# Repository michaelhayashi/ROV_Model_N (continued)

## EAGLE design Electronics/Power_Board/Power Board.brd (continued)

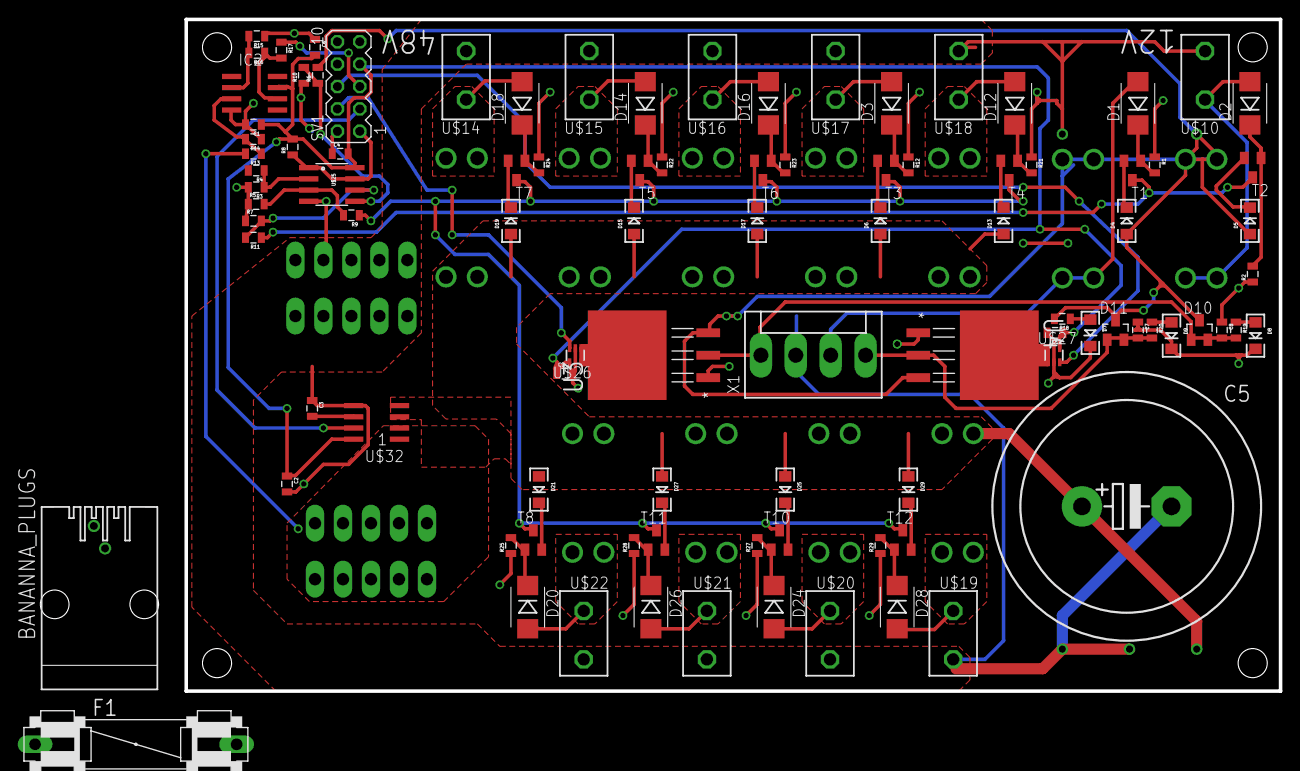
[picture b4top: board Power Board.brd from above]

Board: 2 copper layers, 124.1 x 76.2 mm, 115 parts (1 on the bottom side), 60 nets.

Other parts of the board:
U$23, U$24, U$28, U$29: STAND-OFF

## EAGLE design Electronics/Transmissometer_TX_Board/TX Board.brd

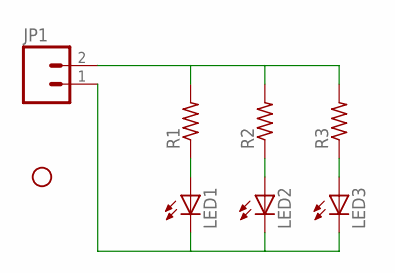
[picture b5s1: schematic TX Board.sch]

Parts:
JP1: M02PTH4; 1X02_XTRA_BIG
JP2: STAND-OFF
LED1, LED2, LED3: LED-FKIT-1206; FKIT-LED-1206
R1, R2, R3: R-US_M1206; M1206

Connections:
GND: JP1.2, R1.2, R2.2, R3.2
unnamed: LED1.A, R1.1
unnamed: LED2.A, R2.1
unnamed: LED3.A, R3.1
unnamed: JP1.1, LED1.C, LED2.C, LED3.C

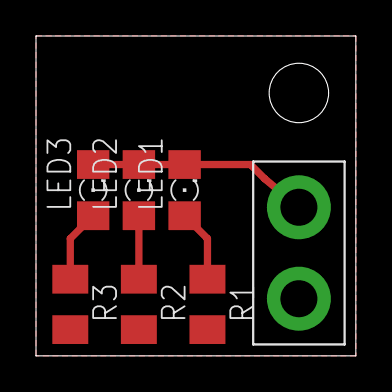
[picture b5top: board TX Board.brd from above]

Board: 2 copper layers, 17.8 x 17.8 mm, 8 parts (0 on the bottom side), 5 nets.

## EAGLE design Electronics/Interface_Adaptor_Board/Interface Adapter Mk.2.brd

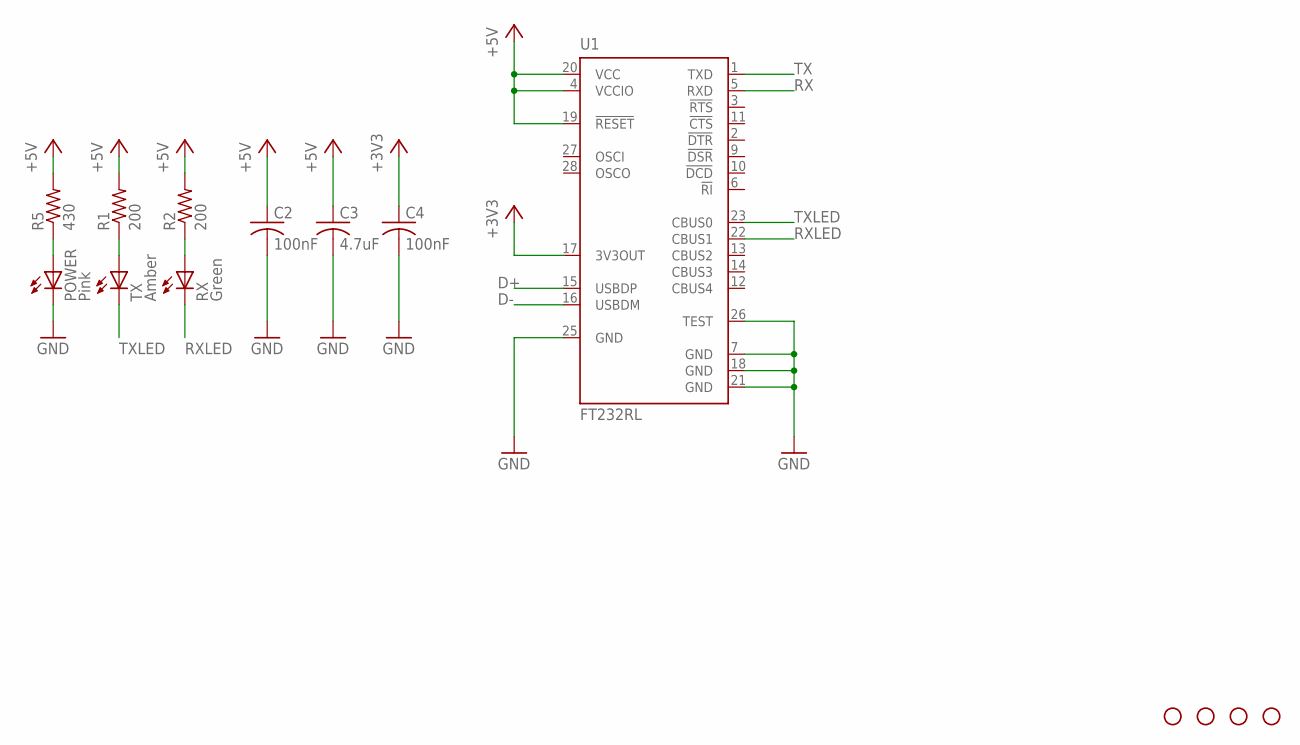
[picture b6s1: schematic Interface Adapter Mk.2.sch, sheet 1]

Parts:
C2, C4: 100nF; C0603
C3: 4.7uF; C0603
JP1, JP2, JP3, JP4: STAND-OFF
POWER: Pink; LED-0603
R1, R2: 200; R0603
R5: 430; R0603
RX: Green; LED-0603
TX: Amber; LED-0603
U1: FT232RL; SSOP28

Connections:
+3V3: C4.1, U1.17 (3V3OUT)
+5V: C2.1, C3.1, R1.2, R2.2, R5.2, U1.4 (VCCIO), U1.19 (!RESET), U1.20 (VCC); also elsewhere on the board
D+: U1.15 (USBDP); also elsewhere on the board
D-: U1.16 (USBDM); also elsewhere on the board
GND: C2.2, C3.2, C4.2, POWER.C, U1.7 (GND), U1.18 (GND), U1.21 (GND), U1.25 (GND), U1.26 (TEST); also elsewhere on the board
unnamed: R1.1, TX.A
unnamed: R2.1, RX.A
unnamed: POWER.A, R5.1
RX: U1.5 (RXD); also elsewhere on the board
RXLED: RX.C, U1.22 (CBUS1)
TX: U1.1 (TXD); also elsewhere on the board
TXLED: TX.C, U1.23 (CBUS0)

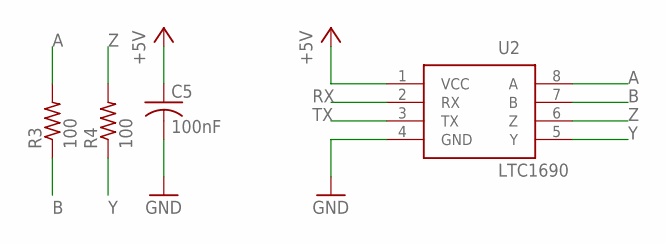
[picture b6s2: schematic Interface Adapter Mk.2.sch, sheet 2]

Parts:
C5: 100nF; C0603
R3, R4: 100; R0603
U2: LTC1690; SOIC-8

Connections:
+5V: C5.1, U2.1 (VCC); also elsewhere on the board
A: R3.2, U2.8 (A); also elsewhere on the board
B: R3.1, U2.7 (B); also elsewhere on the board
GND: C5.2, U2.4 (GND); also elsewhere on the board
RX: U2.2 (RX); also elsewhere on the board
TX: U2.3 (TX); also elsewhere on the board
Y: R4.1, U2.5 (Y); also elsewhere on the board
Z: R4.2, U2.6 (Z); also elsewhere on the board

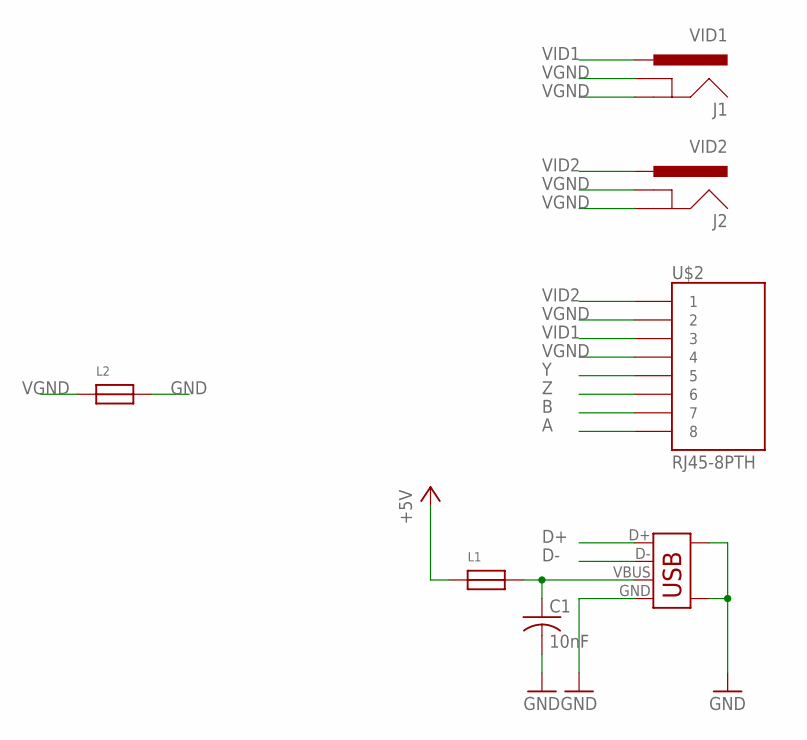
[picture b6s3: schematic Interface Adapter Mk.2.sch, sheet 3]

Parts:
C1: 10nF; C0603
J1: VID1; RCA
J2: VID2; RCA
L1, L2: FERRITE; 0603
U$2: RJ45-8PTH; RJ45-8
X1: USBPTH; USB-B-PTH

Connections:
+5V: L1.1; also elsewhere on the board
A: U$2.8; also elsewhere on the board
B: U$2.7; also elsewhere on the board
D+: X1.D+; also elsewhere on the board
D-: X1.D-; also elsewhere on the board
GND: C1.2, L2.2, X1.GND, X1.P$1, X1.P$2; also elsewhere on the board
unnamed: C1.1, L1.2, X1.VBUS
VGND: J1.BARREL (GND), J1.SPRING (GNDBREAK), J2.BARREL (GND), J2.SPRING (GNDBREAK), L2.1, U$2.2, U$2.4
VID1: J1.BREAK (PWR), U$2.3
VID2: J2.BREAK (PWR), U$2.1
Y: U$2.5; also elsewhere on the board
Z: U$2.6; also elsewhere on the board

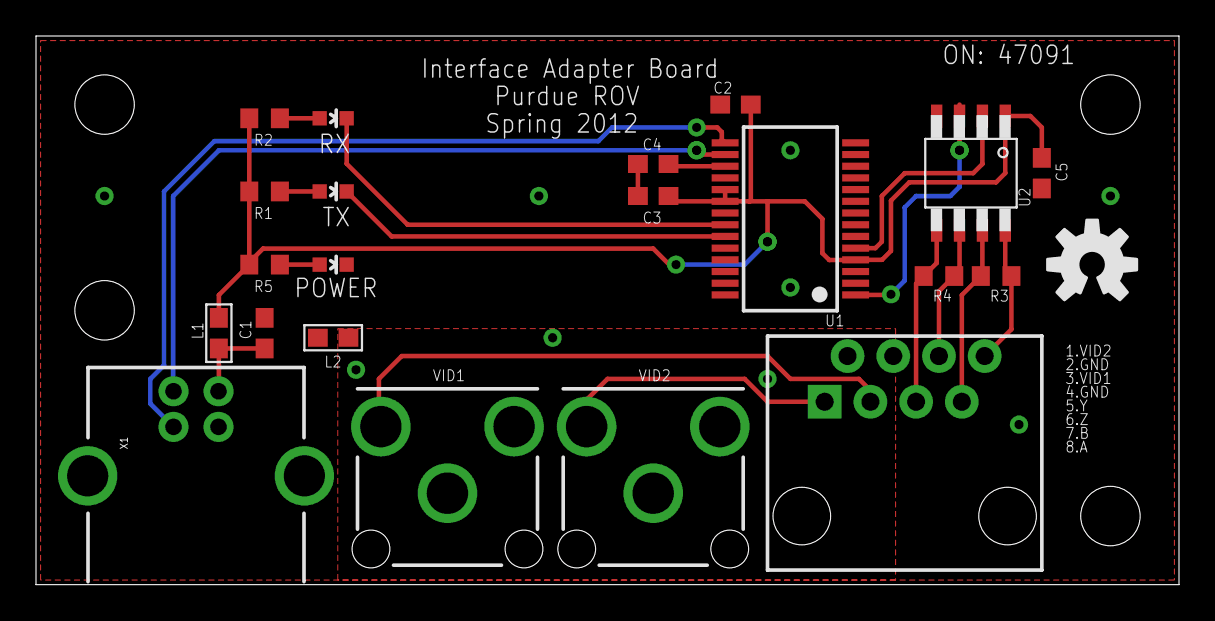
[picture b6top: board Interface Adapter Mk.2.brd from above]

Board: 2 copper layers, 63.5 x 30.5 mm, 26 parts (0 on the bottom side), 20 nets.

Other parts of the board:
U$1: OSHW-LOGO-M

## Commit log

2013-07-29 Update LICENSE
2013-07-30 Primary Files
